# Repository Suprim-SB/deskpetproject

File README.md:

# DESK PET
A desk pet called Starbie. Starbie is a tiny, starry digital pet that replaces traditional buttons with pure gesture control.
<br> 

# WHAT IS IT?
A desk pet is a project that is intended to sit at your desk and add some personality and fun to it. Starbie is an example of a desk pet. It does not really have any other actual use like some other projects do, but it acts as a good way to learn some useful skills needed to advance in the field of electronics while also giving u a cool desk accessory while you are at it. Who doesn't love a cute little pet right? This desk pet is no different. It has different functions depending on what u do with it (Discussed More below). 
<br>
<br>_This build of the pet includes a idle Jellyfish sprite, a shake reaction, tilt controlled radial menu, hidden stats and a extra bubbling effect !_

# WHY?
This project was made to be the project for the week 1 of Hack Club half life. It is me following a guided project as a complete beginner. It is also to learn the basics of hardware and electronics to create more unique projects in the future of my own!
<br>*(This project has a few changes like the microcontroller I used and others, to account for local availability)*

# HOW TO START MAKING?
Starbie is actually not that hard to make!. It just requirs a bit of patience and the eagerness to learn. And it is really customizable too. You can change its shape to whatever you want, add custom functions, reduce complexity if you are a beginner or add even more stuff if you know what your doing. This build of Starbie has the function to detect movement and also the environment!
MATERIALS YOU NEED:
1. Esp32-C3-Supermini (The main microprocessor)
2. DHT11 (The environment sensor)
3. MPU6050 (Gyroscope to detect movement)
4. 10k Ohm Resistor
5. Display OLED SSD1306 128x64 (The display where u actually see your pet)
6. 2x Cherry MX switches; you can use other MX switches too to reduce cost (To control the pet)
7. 2x MX compatible Keycaps

# How the parts fit:
The ESP32-C3 Supermini is the main brains of the project. It is what controls everything else. The dht11 is the environment and humidity sensor. It gives data to the esp which is then processes to perform the task assigned. Same goes for the mpu6050 which gives tilt and movement info. The Switches are to select and control the functions of the pet. The display is the part that actually makes it behave as a pet. It shows a idle jellyfish sprite and also other functions like hearts, or jumping, or bubble trails when interacted it with. <br>_You will see other more unique functions once you actually build it yourself!_

# Project Status
Designing Phase is complete. The physical board is yet to be made, tested , and recorded.
The PCB design, firmware, Schematics, Gerber Files and the BOM are uploaded here.
<br>_Further changes to the modes, features and designs could be added later_

# Project Photos:
Schematic:
<br>

<br>PCB:
<br>

#Bill of Materials:
This bill is mostly fit for the country from where I am building this (Nepal), if if it isn't possible to buy these items from where you are, you could resort to international vendors.
| Item | Link | Price (USD) |
|---|---|---:|
| ESP32-C3-Supermini | [Ekaithau](https://ekaithau.com/products/esp32-c3-mini/) | $5.98 |
| 0.96-inch OLED Display SSD1306 128×64 | [Himalayan Solutions](https://himalayansolution.com/product/0-96-inch-oled-display-white) | $3.32 |
| DHT11 Temperature and Humidity Sensor | [Himalayan Solutions](https://himalayansolution.com/product/dht11-temperature-and-humidity-sensor) | $0.66 |
| GY-521 MPU6050 Accelerometer and Gyroscope | [Himalayan Solutions](https://himalayansolution.com/product/mpu-6050-module) | $2.33 |
| Keycaps (Pack of 21) (×1) | [Aliexpress](https://www.aliexpress.com/item/1005012239749346.html?spm=a2g0o.productlist.main.3.3f144d549mz35h&algo_pvid=506c8727-3e36-41af-bb6c-d233ef1303f6&algo_exp_id=506c8727-3e36-41af-bb6c-d233ef1303f6-2&pdp_ext_f=%7B%22order%22%3A%2215%22%2C%22eval%22%3A%221%22%2C%22fromPage%22%3A%22search%22%7D&pdp_npi=6%40dis%21NPR%211280.25%21163.79%21%21%218.52%211.09%21%402101528c17943132790031985e0ef3%2112000057855706932%21sea%21NP%216050325592%21ABX%211%210%21n_tag%3A-29910%3Bd%3A4b5c7ce9%3Bm03_new_user%3A-29895%3BpisId%3A5000000219357547&curPageLogUid=ADOSwM0hiseN&utparam-url=scene%3Asearch%7Cquery_from%3A%7Cx_object_id%3A1005012239749346%7C_p_origin_prod%3A) | $1.10 |
| HMX Taro Ball Linear Switch (×2) | [ErgoKeys Nepal](https://ergokeysnepal.com/product/hmx-taro-ball-linear-switch/) | $0.84 |
| **Total** | | **$14.9** _(Including shipping from Ekaithu and Himalayan Solutions)_|

_Prices may fluctuate_
<br>**PCB prices (JLCPCB)**
<br> PCB price = $4
<br> Delivery fee (the reasonably priced one takes long 18-24 days) = $13.30 ; E-Post
<br> Total = $17.30 (but with a coupon for new user it becomes 13.30)
<br> *I was going to order two pcbs at the same time and get divide the shipping fee but since the second project wont get approved by then, i will not be able to do so*
<br>**TOTAL (Including Shipping)** = 28.2$

<br> 

<br> 
<br> 
<br>

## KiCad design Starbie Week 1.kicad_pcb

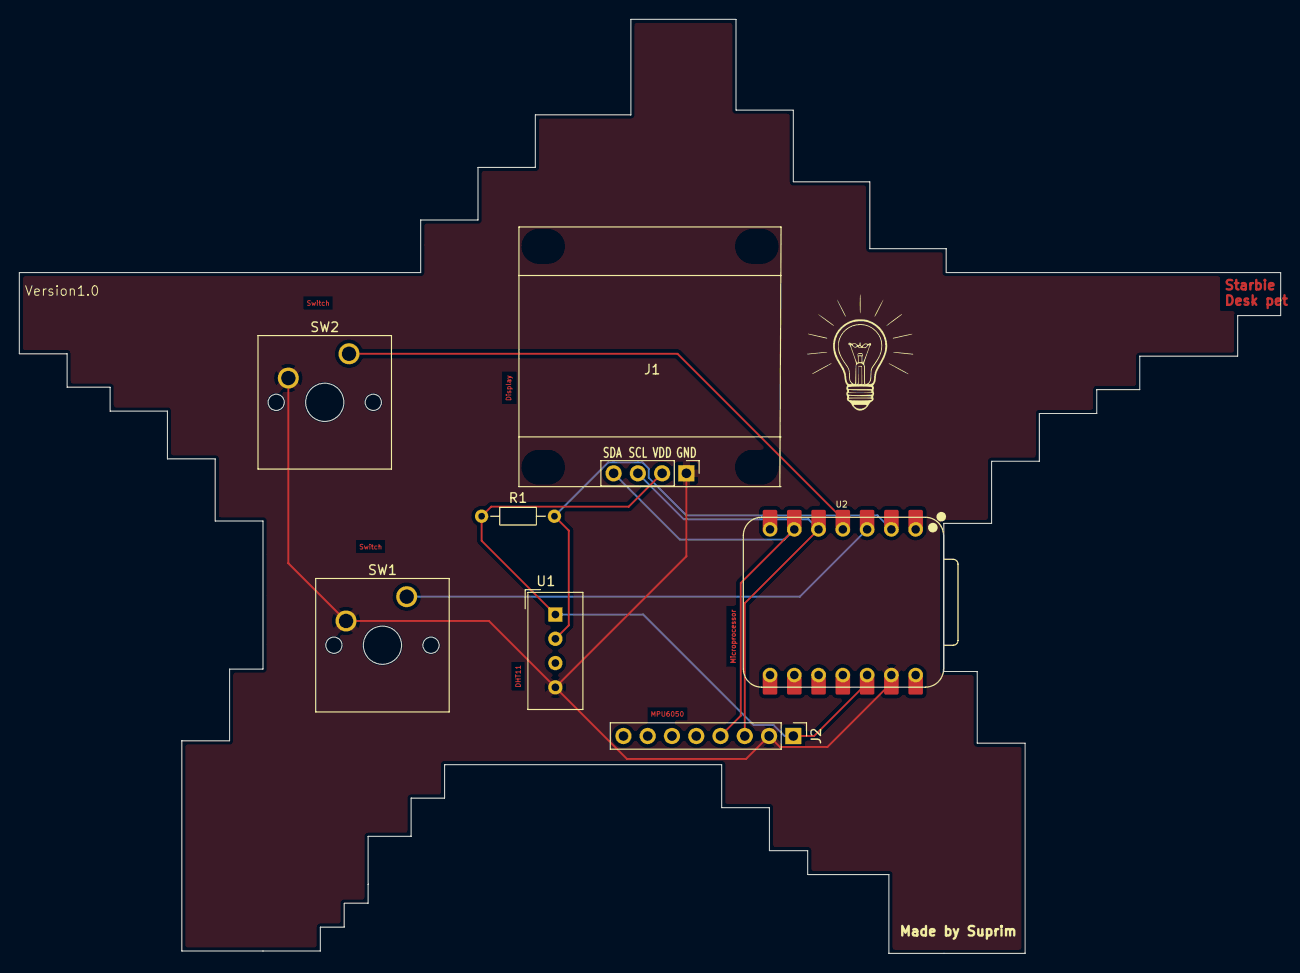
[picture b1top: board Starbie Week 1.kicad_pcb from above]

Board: 2 copper layers, 132.0 x 97.8 mm, 8 parts (0 on the bottom side), 7 nets.

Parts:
.: LOGO
J1: Display; Display_128x64_096_I2C
J2: MPU; PinHeader_1x08_P2.54mm_Vertical
R1: 10k; R_Axial_DIN0204_L3.6mm_D1.6mm_P7.62mm_Horizontal
SW1, SW2: SW_Push; SW_Cherry_MX_1.00u_PCB
U1: DHT11; Aosong_DHT11_5.5x12.0_P2.54mm
U2: XIAO-ESP32-C3-SMD; XIAO-ESP32-C6-DIP

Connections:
+3.3V: J1.2, J2.1, R1.1, U1.1 (VDD), U2.12 (3V3_OUT)
/DHT11 DATA: R1.2, U1.2 (DATA), U2.2 (D1)
/GPIO2: SW1.1, U2.3 (D2)
/GPIO3: SW2.1, U2.4 (D3)
/SCL: J1.3, J2.3, U2.5 (D4)
/SDA: J1.4, J2.4, U2.6 (D5)
GND: J1.1, J2.2, SW1.2, SW2.2, U1.4 (GND), U2.13 (GND)

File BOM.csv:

Item,Qty,Supplier,Cost/item,Total Cost,link
Seeed Studio XIAO ESP32-S3,1,Daraz Nepal,$9.56,$9.56,https://www.daraz.com.np/products/i1546190932-s12368458639.html
0.96-inch OLED Display SSD1306 128×64,1,GIGA Nepal,$3.87,$3.87,https://www.giganepal.com/product/0-96-inch-oled-display/
DHT11 Temperature and Humidity Sensor,1,GIGA Nepal,$1.93,$1.93,https://www.giganepal.com/product/temperature-humidity-senso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
GY-521 MPU6050 Accelerometer and Gyroscope,1,GIGA Nepal,$3.22,$3.22,https://www.giganepal.com/product/mpu6050-3-axis-acceleromet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
DIY DSA Keycap (×2),2,Daraz Nepal,$1.30,$2.60,https://www.daraz.com.np/mechanical-keyboard-accessories-diy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
HMX Taro Ball Linear Switch (×2),2,ErgoKeysNepal,$0.42,$0.84,https://ergokeysnepal.com/product/hmx-taro-ball-linear-switch/
PCB,5,JLCPCB,$2.00,$10.00,https://cart.jlcpcb.com/quote?stencilLayer=2&stencilWidth=13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
Estimated total shipping,1,,,$0.00,

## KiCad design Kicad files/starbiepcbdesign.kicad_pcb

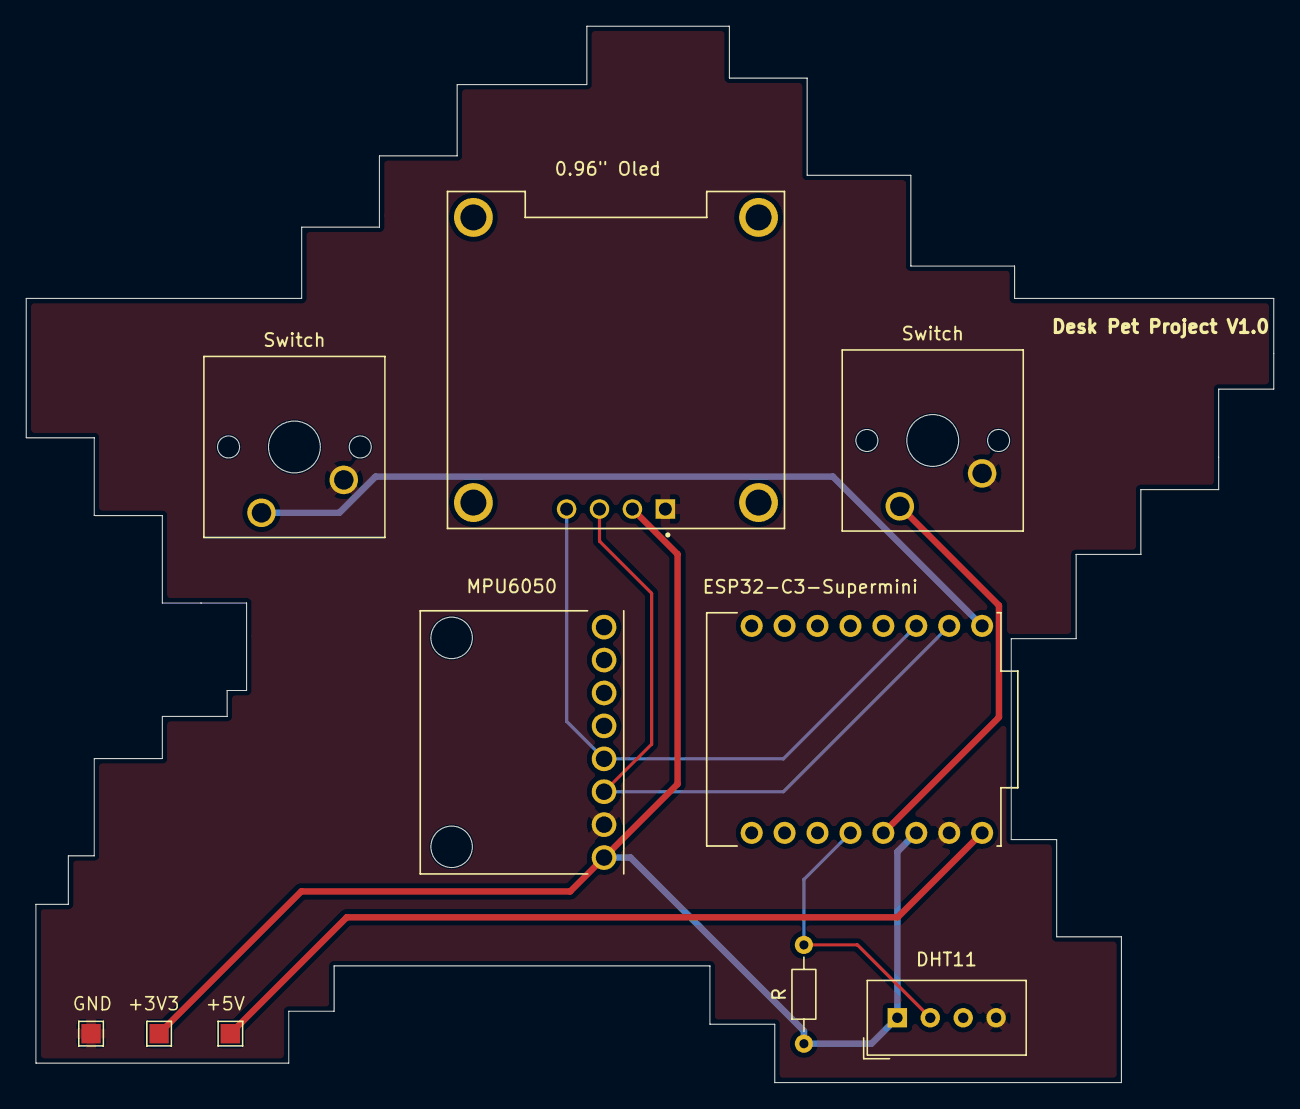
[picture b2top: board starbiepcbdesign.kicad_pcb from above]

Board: 2 copper layers, 96.2 x 81.5 mm, 10 parts (0 on the bottom side), 8 nets.

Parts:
R: 10k; R_Axial_DIN0204_L3.6mm_D1.6mm_P7.62mm_Horizontal
SW1, SW2: Switch; SW_Cherry_MX_1.00u_PCB
TP1: GND; TestPoint_Pad_1.5x1.5mm
TP2: +3V3; TestPoint_Pad_1.5x1.5mm
TP3: +5V; TestPoint_Pad_1.5x1.5mm
U1: DHT11; Aosong_DHT11_5.5x12.0_P2.54mm
U2: MPU6050; MODULE_OC09600
U3: ESP32-C3-Supermini; MODULE_ESP32-C3_SUPERMINI
U4: 0.96" Oled; MODULE_DM-OLED096-636

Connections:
+3V3: R.1, TP2.1 (1_1), U1.1 (VCC), U2.VCC, U3.3.3 (3V3), U4.2 (VCC_IN)
+5V: TP3.1 (1_1), U3.5V
/DHT11 DATA: R.2, U1.2 (DATA), U3.3 (GPIO3)
/GPIO2: SW1.1, U3.4 (GPIO4)
/GPIO3: SW2.1, U3.5 (GPIO5)
/SCL: U2.SCL, U3.6 (GPIO6), U4.3 (SCL)
/SDA: U2.SDA, U3.7 (GPIO7), U4.4 (SDA)
GND: SW1.2, SW2.2, TP1.1 (1_1), U1.4 (GND), U2.GND, U3.G (GND), U4.1 (GND)

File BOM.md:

# Starbie – bill of materials

<!-- Generated by Half Life from project cmuv9q1qn0fcp01smvtev21ch. Edits here are overwritten on the next sync. -->
<!-- Generated: 2026-10-11T18:09:43.251Z -->

> [!NOTE]
> This parts list is mirrored from [Half Life](https://halflife.hackclub.com). Editing it here will not change the platform's copy, and the next sync overwrites this file.

| Week | Tier | Parts funding |
| --- | --- | --- |
| Week 1 | Tier 1 | $30.00 |

| Part | What it's for | Qty | Unit | Total | Vendor |
| --- | --- | --- | --- | --- | --- |
| [Seeed Studio XIAO ESP32-S3](https://www.daraz.com.np/products/i1546190932-s12368458639.html) | The main microprocessor | 1 | $9.56 | $9.56 | [Daraz Nepal](https://www.daraz.com.np/products/i1546190932-s12368458639.html) |
| [0.96-inch OLED Display SSD1306 128×64](https://www.giganepal.com/product/0-96-inch-oled-display/) | The display to show stuff | 1 | $3.87 | $3.87 | [GIGA Nepal](https://www.giganepal.com/product/0-96-inch-oled-display/) |
| [DHT11 Temperature and Humidity Sensor](https://www.giganepal.com/product/temperature-humidity-senso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 | The environment sensor | 1 | $1.93 | $1.93 | [GIGA Nepal](https://www.giganepal.com/product/temperature-humidity-senso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 |
| [GY-521 MPU6050 Accelerometer and Gyroscope](https://www.giganepal.com/product/mpu6050-3-axis-acceleromet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 | The motion sensor | 1 | $3.22 | $3.22 | [GIGA Nepal](https://www.giganepal.com/product/mpu6050-3-axis-acceleromet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 |
| [DIY DSA Keycap (×2)](https://www.daraz.com.np/mechanical-keyboard-accessories-diy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 | The keycaps for the switches | 2 | $1.30 | $2.60 | [Daraz Nepal](https://www.daraz.com.np/mechanical-keyboard-accessories-diy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 |
| [HMX Taro Ball Linear Switch (×2)](https://ergokeysnepal.com/product/hmx-taro-ball-linear-switch/) | The switches | 2 | $0.42 | $0.84 | [ErgoKeysNepal](https://ergokeysnepal.com/product/hmx-taro-ball-linear-switch/) |
| [PCB](https://cart.jlcpcb.com/quote?stencilLayer=2&stencilWidth=13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 | the main board | 5 | $2.00 | $10.00 | [JLCPCB](https://cart.jlcpcb.com/quote?stencilLayer=2&stencilWidth=13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 |
| **Parts subtotal** | — | — | — | **$32.02** | — |
| **Tax & shipping** | — | — | — | **$0.00** | — |
| **Total** | — | — | — | **$32.02** | — |

**$2.02 over the tier's funding.** Every tier gives a fixed amount for parts, so this needs cutting back or a higher tier.

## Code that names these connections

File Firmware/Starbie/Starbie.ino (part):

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
// --- Your board's pins ----------------------------------------------------
// These are ESP32-C3 SuperMini GPIO numbers (they match the schematic).
const int I2C_SDA_PIN = 7;       // GPIO7: OLED + MPU6050 SDA
const int I2C_SCL_PIN = 6;       // GPIO6: OLED + MPU6050 SCL
const int DHT_PIN = 3;           // GPIO3: DHT11 data
const int BUTTON_ONE_PIN = 4;    // GPIO4 (SW1): opens/confirms the radial menu
const int BUTTON_TWO_PIN = 5;    // GPIO5 (SW2): shows/hides stats

// Set this to false if your submission does not have a DHT11.
const bool USE_DHT11 = true;
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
